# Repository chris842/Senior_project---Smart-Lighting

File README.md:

# Smart Lighting v1.0.0
This is the Smart Lighting project for my senior project.

DESCRIPTION
---------------------------------------------------------
This project includes the details for the smart lighting project, such as how it will function,
the specific componenets of the project, as well as some additional features such as the housing
design and PCB designs.

The programming languaged used for the project was C++, which was written using VSCode and PlatformIO
(More details on the code can be found on the main.cpp file). The microcontroller used for this project
was the ESP32 devkit v1, allowing for wireless connections to be made.

ADDITIONAL NOTES
----------------------------------------------------------
For the PCB design, there were some components that I had to customize myself, as KiCAD did not have the 
specific componenets that I had in mind. These additional symbols and components should be included in the
ZIP file.
Also note that the app used to communicate with the ESP32 is Blynk. Currently, the app that I had created
cannot be published as a standalone, as the BLE features for Blynk is still in its prototyping phase. In order to
recreate this project, using the Blynk app is necessary to have the manual control feature operational.

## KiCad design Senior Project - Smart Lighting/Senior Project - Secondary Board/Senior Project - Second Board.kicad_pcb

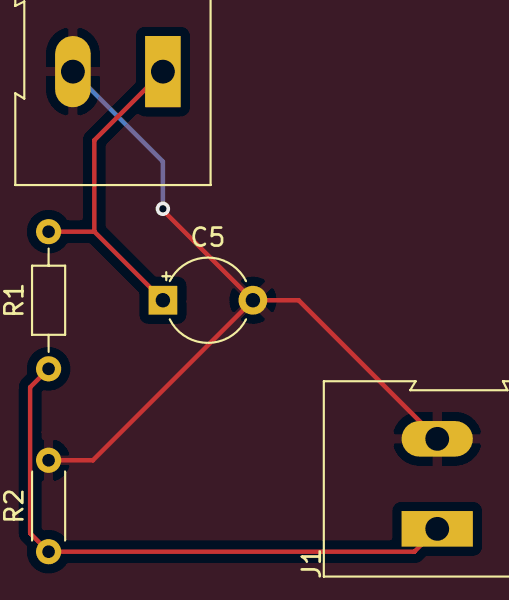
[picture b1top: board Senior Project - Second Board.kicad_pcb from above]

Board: 2 copper layers, 4 parts (0 on the bottom side), 3 nets.

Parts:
C5: 0.1; CP_Radial_Tantal_D4.5mm_P5.00mm
J1: Light Sensor Output; TerminalBlock_Altech_AK300-2_P5.00mm
R1: 1k; R_Axial_DIN0204_L3.6mm_D1.6mm_P7.62mm_Horizontal
R2: R_PHOTO; R_Axial_DIN0204_L3.6mm_D1.6mm_P5.08mm_Horizontal

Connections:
GND: C5.2, J1.2, R2.2
unnamed: C5.1, R1.2
unnamed: J1.1, R1.1, R2.1

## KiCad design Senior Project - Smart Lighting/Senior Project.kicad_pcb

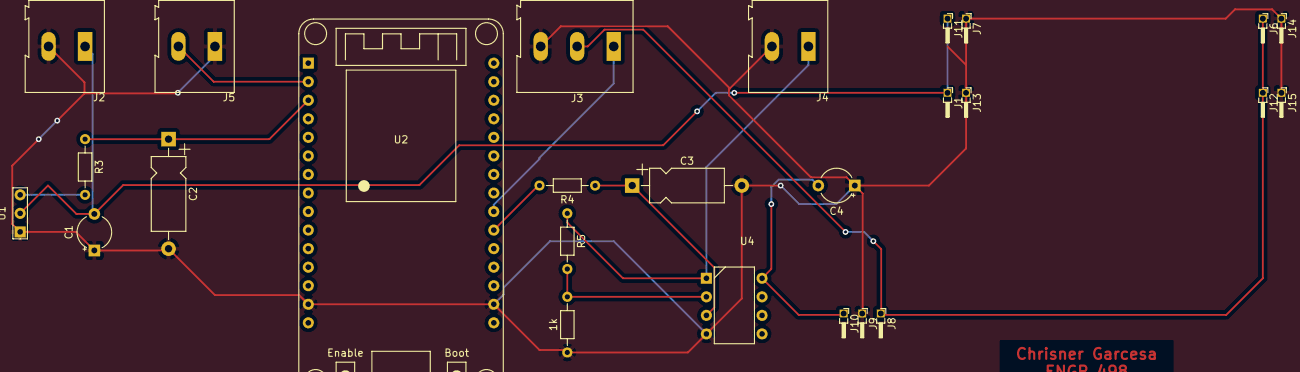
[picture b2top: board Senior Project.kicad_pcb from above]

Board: 2 copper layers, 26 parts (0 on the bottom side), 12 nets.

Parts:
1k: R; R_Axial_DIN0204_L3.6mm_D1.6mm_P7.62mm_Horizontal
C1: 0.1u; CP_Radial_Tantal_D4.5mm_P5.00mm
C2: 20u; CP_Axial_L10.0mm_D4.5mm_P15.00mm_Horizontal
C3: 1000u; CP_Axial_L10.0mm_D4.5mm_P15.00mm_Horizontal
C4: 0.1; CP_Radial_Tantal_D4.5mm_P5.00mm
J1, J6, J7, J8, J9, J10, J11, J12, J13, J14, J15: Conn_01x01; PinHeader_1x01_P1.00mm_Horizontal
J2, J4, J5: Screw_Terminal_01x02; TerminalBlock_Altech_AK300-2_P5.00mm
J3: Screw_Terminal_01x03; TerminalBlock_Altech_AK300-3_P5.00mm
R3: 20k; R_Axial_DIN0204_L3.6mm_D1.6mm_P7.62mm_Horizontal
R4: 1k; R_Axial_DIN0204_L3.6mm_D1.6mm_P7.62mm_Horizontal
R5: 2k; R_Axial_DIN0204_L3.6mm_D1.6mm_P7.62mm_Horizontal
U1: PIRSensor; PIR Sensor
U2: ESP32_DevKit_V1_DOIT; esp32_devkit_v1_doit
U4: LM358; LM358P

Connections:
+3V3: C1.2, J1.1, J2.1, J11.1, U1.2
+5V: J3.2, J6.1, J8.1, J12.1
GND: 1k.1, C1.1, C2.2, C3.2, C4.1, J2.2, J3.3, J4.2, J5.1, J7.1, J9.1, J13.1, J14.1, J15.1, U1.1, U2.14, U2.17, U4.4
unnamed: 1k.2, R5.2, U4.2
unnamed: C2.1, R3.1, U2.3
unnamed: C3.1, R4.1, U4.3
unnamed: C4.2, J10.1, U4.8
unnamed: J3.1, U2.22
unnamed: J4.1, R5.1, U4.1
unnamed: J5.2, U2.2
unnamed: R3.2, U1.3
unnamed: R4.2, U2.21
